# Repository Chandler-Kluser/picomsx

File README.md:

# Pico MSX

This is NOT [msxpico](https://github.com/jeroentaverne/msxpico) project!

The main reason this project exists is that [msxpico](https://github.com/jeroentaverne/msxpico) is closed source, feel free to build firmware, make contributions or redistributing this project freely!

## Features

For now, the main goal of this project is to make a flashcart only, in later phases it gain more features.

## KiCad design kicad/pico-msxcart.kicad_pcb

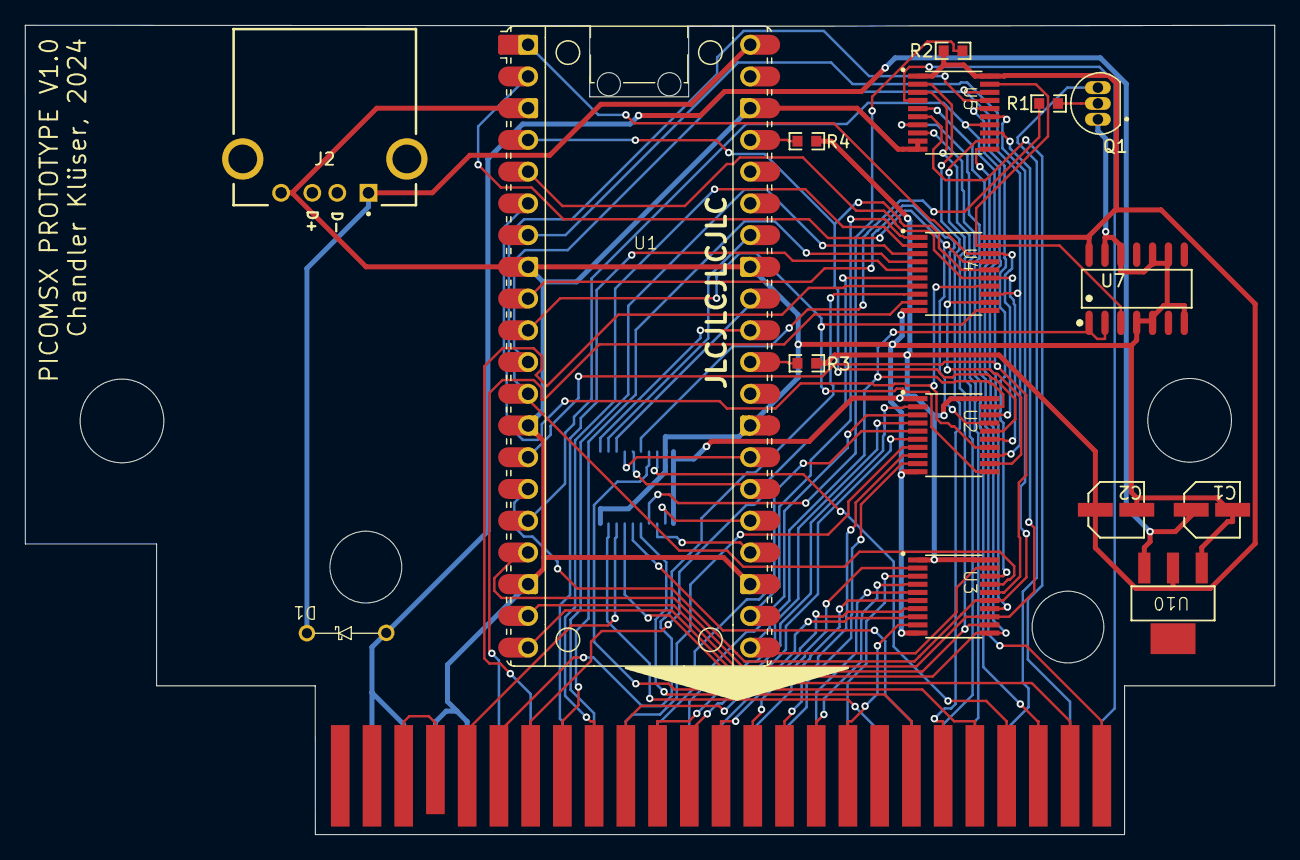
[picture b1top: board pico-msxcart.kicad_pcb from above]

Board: 2 copper layers, 100.0 x 64.8 mm, 18 parts (1 on the bottom side), 75 nets.

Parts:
C1, C2: SMD_CAP
D1: DS14 SOD-123FL; SCHOTKKY_THT
J1: MSX-CONNECTOR; MSXCART
J2: USB-A
Q1: 2N3904
R1, R2, R3, R4: 2k2; R0603
U1: RaspberryPi_Pico; RP2040_COMMON
U2, U3, U4, U5, U6: TSSOP-20
U7: SOP-14
U10: AMS1117-3.3; AMS1117-3V3

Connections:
3V3_EN: R4.1, U1.37 (3V3_EN)
A0: J1.28 (A0), U2.2 (A0)
A1: J1.27 (A1), U2.3 (A1)
A2: J1.30 (A2), U2.4 (A2)
A3: J1.29 (A3), U2.5 (A3)
A4: J1.32 (A4), U2.6 (A4)
A5: J1.31 (A5), U2.7 (A5)
A6: J1.22 (A6), U2.8 (A6)
A7: J1.21 (A7), U2.9 (A7)
A8: J1.24 (A8), U3.2 (A0)
A9: J1.17 (A9), U3.3 (A1)
A10: J1.20 (A10), U3.4 (A2)
A11: J1.19 (A11), U3.5 (A3)
A12: J1.23 (A12), U3.6 (A4)
A13: J1.26 (A13), U3.7 (A5)
A14: J1.25 (A14), U3.8 (A6)
A15: J1.18 (A15), U3.9 (A7)
BUSDIR: J1.10 (~BUSDIR), U6.17 (B1)
BUSDIR3V3: U1.24 (GPIO18), U6.3 (A1)
CLOCK: J1.42 (CLOCK), U6.8 (A6)
CLOCK_3V3: U1.34 (GPIO28_ADC2), U6.12 (B6)
CS1: J1.1 (~CS1), U5.4 (A2)
CS2: J1.2 (~CS2), U5.5 (A3)
CS12: J1.3 (~CS12), U5.6 (A4)
D0: J1.34 (D0), U4.2 (A0)
D1: J1.33 (D1), U4.3 (A1)
D2: J1.36 (D2), U4.4 (A2)
D3: J1.35 (D3), U4.5 (A3)
D4: J1.38 (D4), U4.6 (A4)
D5: J1.37 (D5), U4.7 (A5)
D6: J1.40 (D6), U4.8 (A6)
D7: J1.39 (D7), U4.9 (A7)
DATADIR: U1.22 (GPIO17), U4.1 (DIR)
GND: C1.2, C2.2, J1.41 (GND@1), J1.43 (GND@2), J2.04 (GND), Q1.1, U1.3 (GND), U1.8 (GND), U1.13 (GND), U1.18 (GND), U1.23 (GND), U1.28 (GND), U1.33 (AGND), U1.38 (GND), U2.10 (GND), U3.10 (GND), U4.10 (GND), U5.9 (A7), U5.10 (GND), U6.10 (GND), U6.19 (~OE), U7.4 (2A), U7.5 (2B), U7.7 (GND), U7.9 (3A), U7.10 (3B), U7.12 (4A), U7.13 (4B), U10.1 (ADJ(GND))
INT: J1.8 (~INT), U6.18 (B0)
INT3V3: U1.25 (GPIO19), U6.2 (A0)
IORQ: J1.11 (~IORQ), U5.3 (A1)
M1: J1.9 (M1), U5.8 (A6)
MERQ: J1.12 (~MERQ), U5.2 (A0)
MP0_3V3: U1.1 (GPIO0), U2.18 (B0), U4.18 (B0)
MP1_3V3: U1.2 (GPIO1), U2.17 (B1), U4.17 (B1)
MP2_3V3: U1.4 (GPIO2), U2.16 (B2), U4.16 (B2)
MP3_3V3: U1.5 (GPIO3), U2.15 (B3), U4.15 (B3)
MP4_3V3: U1.6 (GPIO4), U2.14 (B4), U4.14 (B4)
MP5_3V3: U1.7 (GPIO5), U2.13 (B5), U4.13 (B5)
MP6_3V3: U1.9 (GPIO6), U2.12 (B6), U4.12 (B6)
MP7_3V3: U1.10 (GPIO7), U2.11 (B7), U4.11 (B7)
MP8_3V3: U1.11 (GPIO8), U3.18 (B0), U5.18 (B0)
MP9_3V3: U1.12 (GPIO9), U3.17 (B1), U5.17 (B1)
MP10_3V3: U1.14 (GPIO10), U3.16 (B2), U5.16 (B2)
MP11_3V3: U1.15 (GPIO11), U3.15 (B3), U5.15 (B3)
MP12_3V3: U1.16 (GPIO12), U3.14 (B4), U5.14 (B4)
MP13_3V3: U1.17 (GPIO13), U3.13 (B5), U5.13 (B5)
MP14_3V3: U1.19 (GPIO14), U3.12 (B6), U5.12 (B6)
MP15_3V3: U1.20 (GPIO15), U3.11 (B7), U5.11 (B7)
MSEL0_3V3: U1.21 (GPIO16), U2.19 (~OE), U3.19 (~OE), U7.1 (1A), U7.2 (1B)
MSEL1_3V3: U4.19 (~OE), U5.19 (~OE), U7.3 (1Y)
unnamed: J1.44 (SW1), J1.46 (SW2)
unnamed: Q1.2, R1.2
unnamed: R1.1, U6.16 (B2)
RD: J1.14 (~RD), U6.5 (A3)
RD_3V3: U1.26 (GPIO20), U6.15 (B3)
RESET: J1.15 (~RESET), U6.9 (A7)
RESET_3V3: U1.31 (GPIO26_ADC0), U6.11 (B7)
RFSH: J1.6 (~RFSH), U5.7 (A5)
RUN: R3.1, U1.30 (RUN)
SLTSL: J1.4 (~SLTSL), U6.7 (A5)
SLTSL_3V3: U1.32 (GPIO27_ADC1), U6.13 (B5)
VCC: C1.1, D1.2 (A), J1.45 (5V@1), J1.47 (5V@2), U10.3 (VIN)
VCC_3V3: C2.1, R2.2, R3.2, R4.2, U2.1 (DIR), U2.20 (VCC), U3.1 (DIR), U3.20 (VCC), U4.20 (VCC), U5.1 (DIR), U5.20 (VCC), U6.1 (DIR), U6.20 (VCC), U7.14 (VCC), U10.2 (VOUT(TAB))
VCC_4V7: D1.1 (K), J2.01 (VCC), U1.40 (VBUS)
WAIT: J1.7 (/WAIT), Q1.3
WAIT3V3: R2.1, U6.4 (A2)
WR: J1.13 (~WR), U6.6 (A4)
WR_3V3: U1.27 (GPIO21), U6.14 (B4)

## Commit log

2024-04-22 Fix README
2024-04-22 PCB Revision v0.1.0
2024-04-23 Switched to Patola Board
